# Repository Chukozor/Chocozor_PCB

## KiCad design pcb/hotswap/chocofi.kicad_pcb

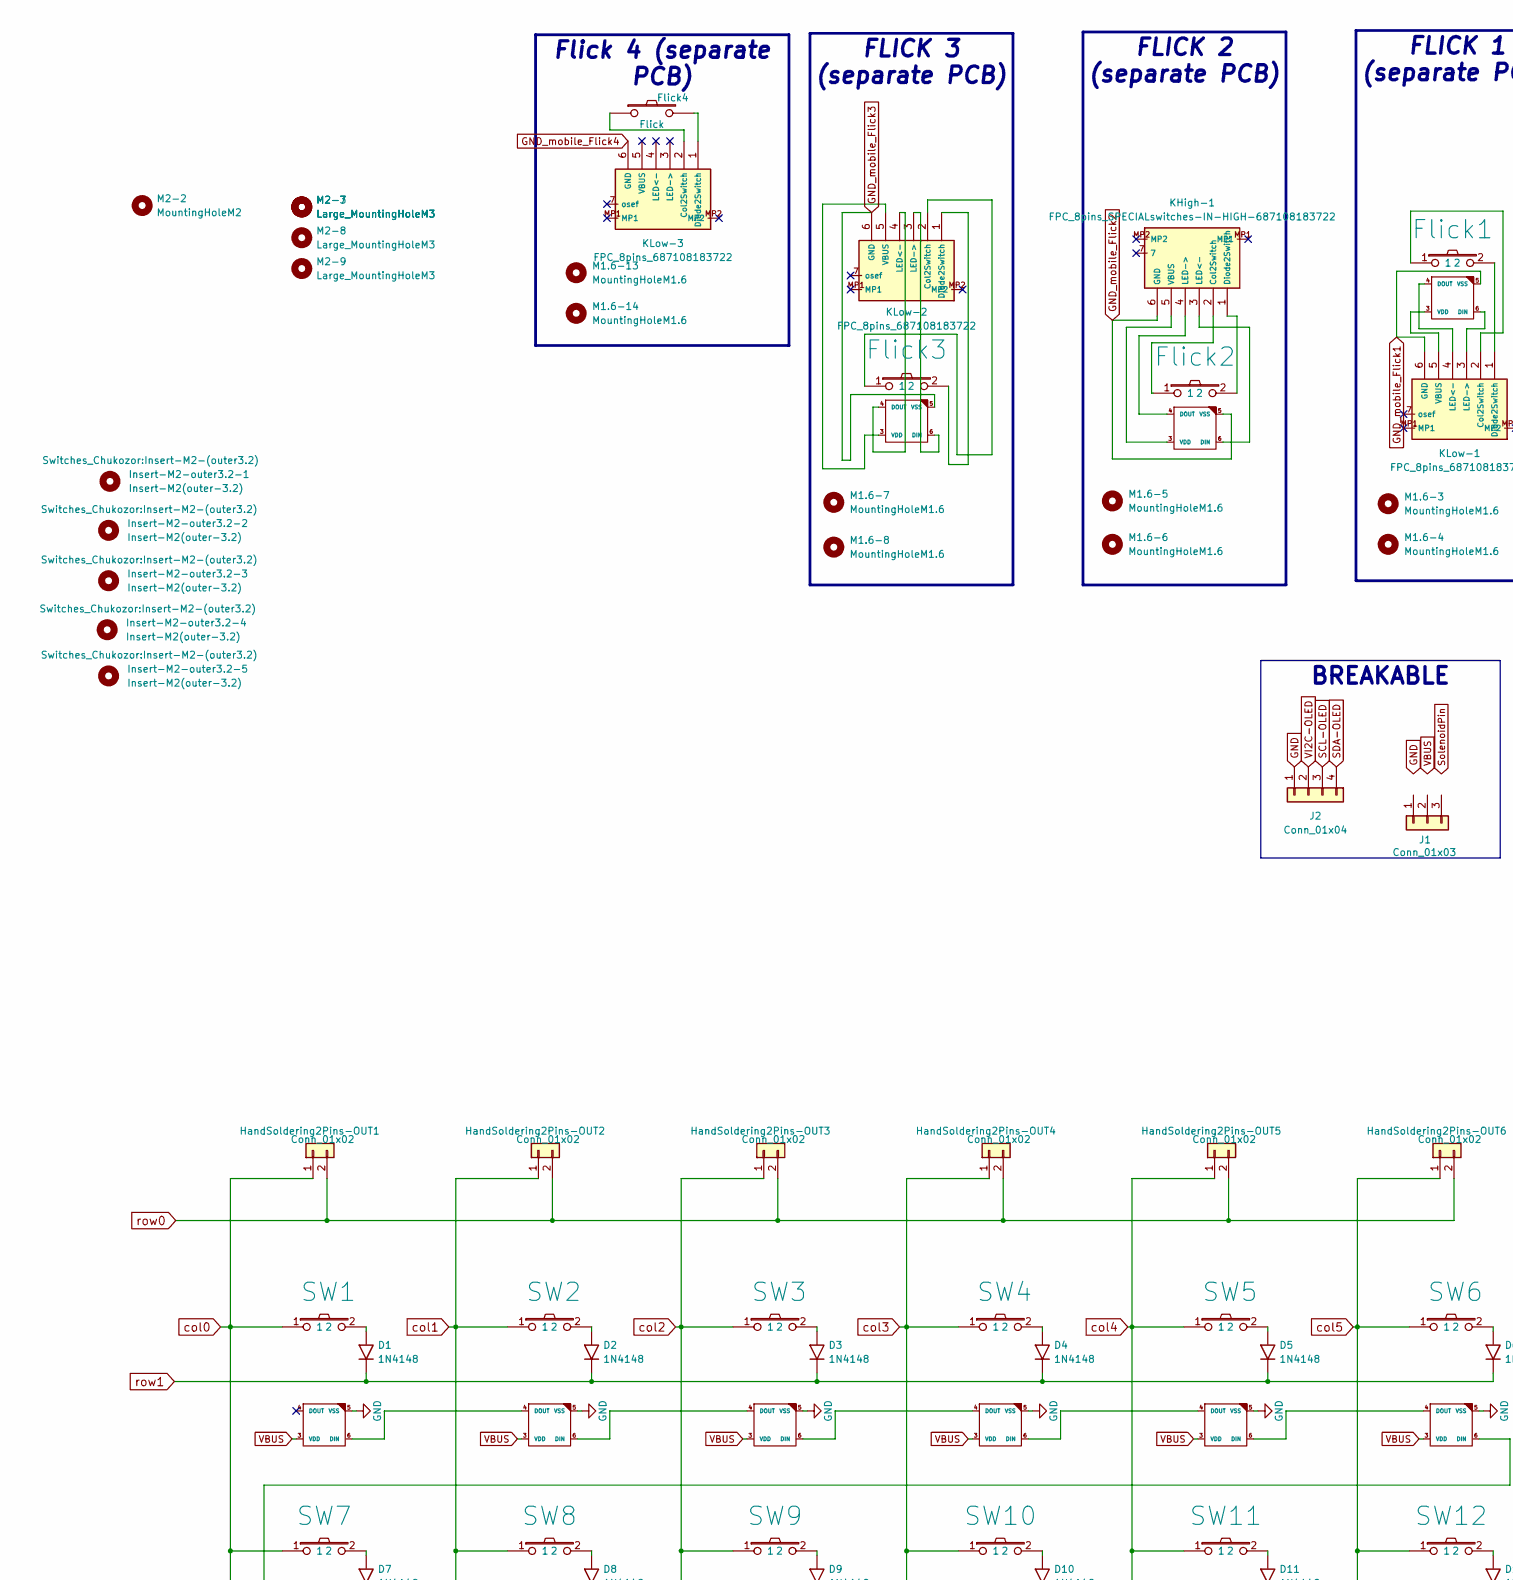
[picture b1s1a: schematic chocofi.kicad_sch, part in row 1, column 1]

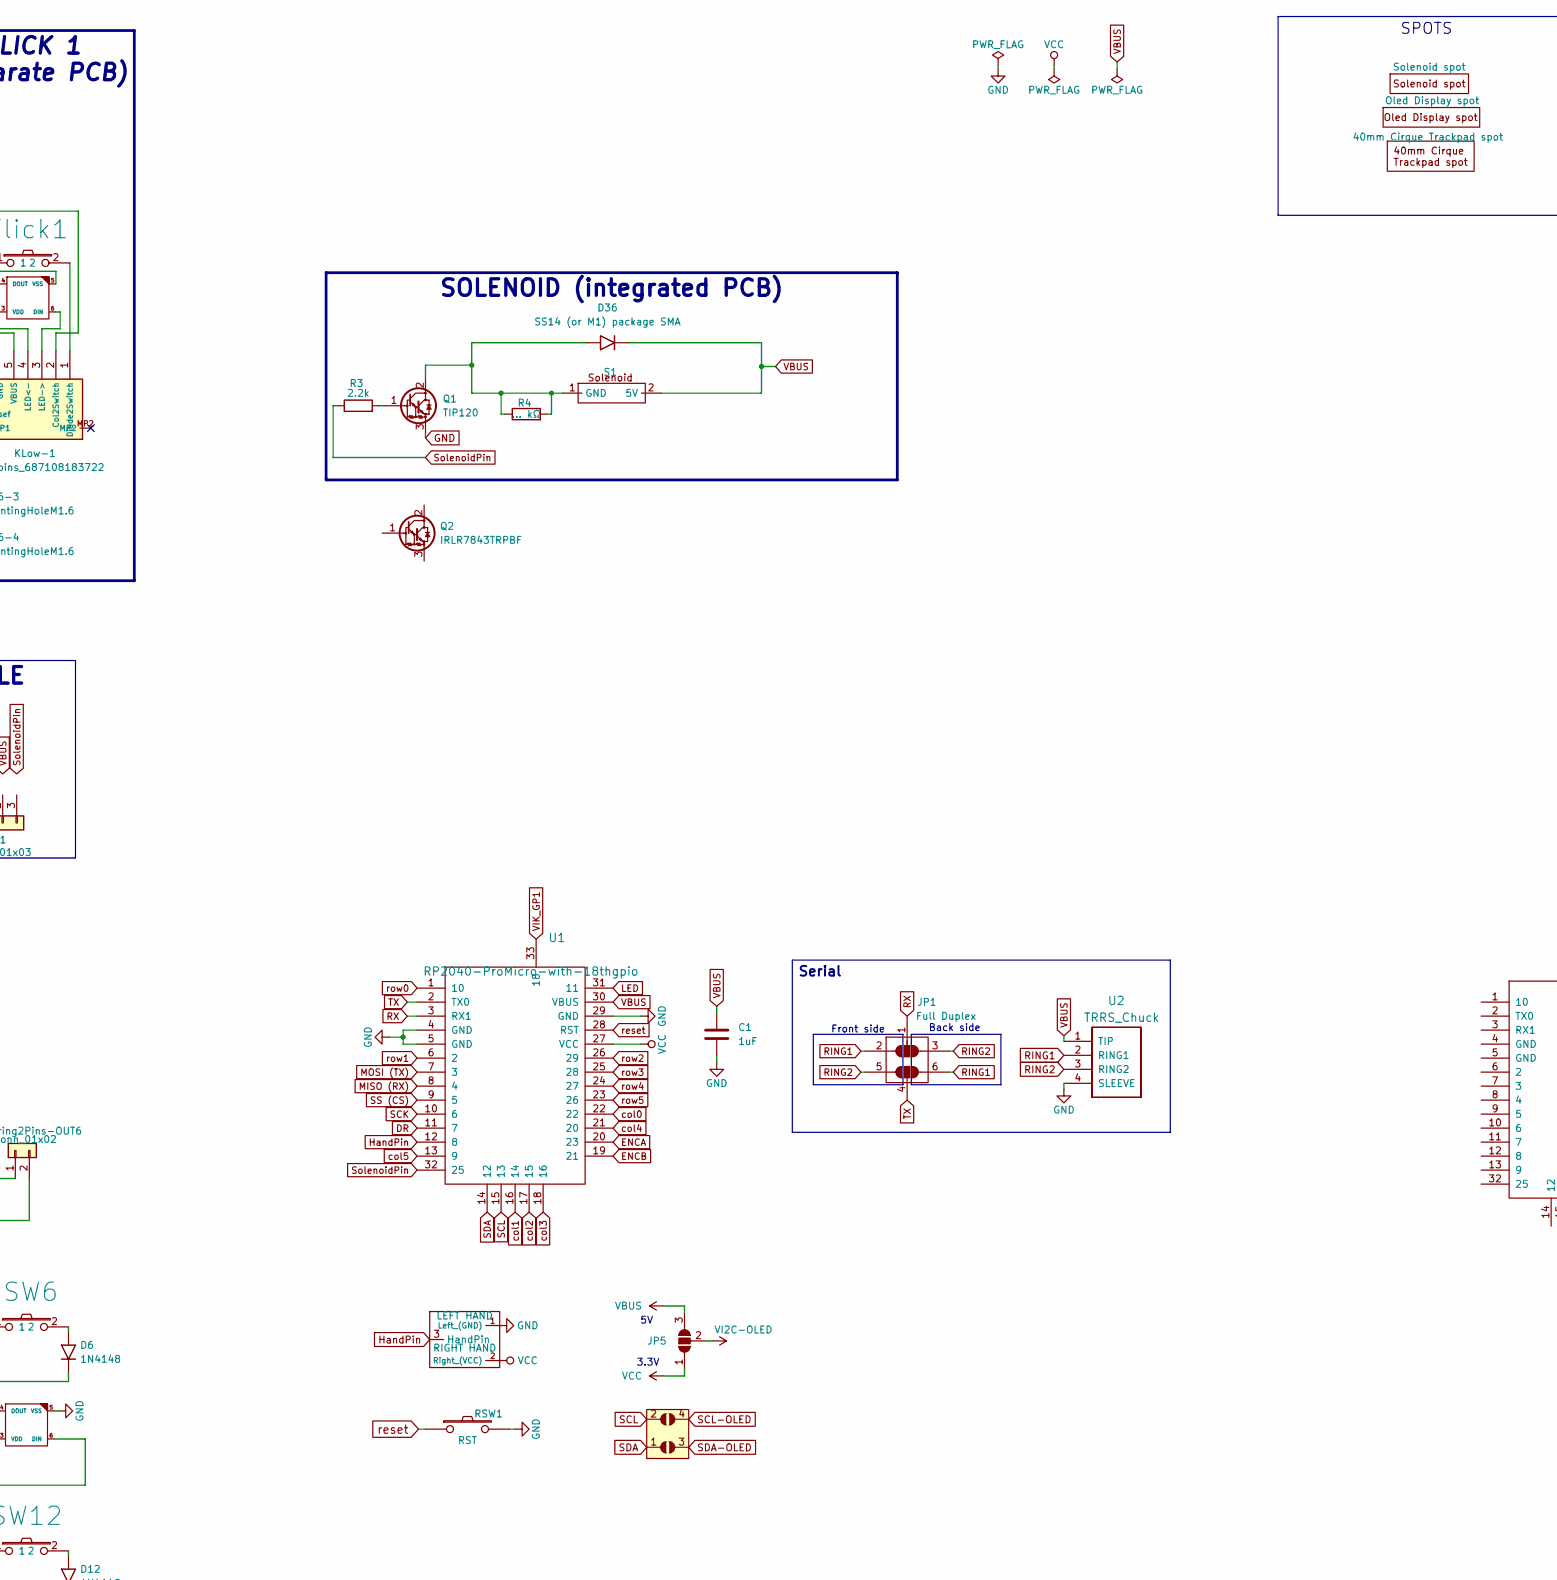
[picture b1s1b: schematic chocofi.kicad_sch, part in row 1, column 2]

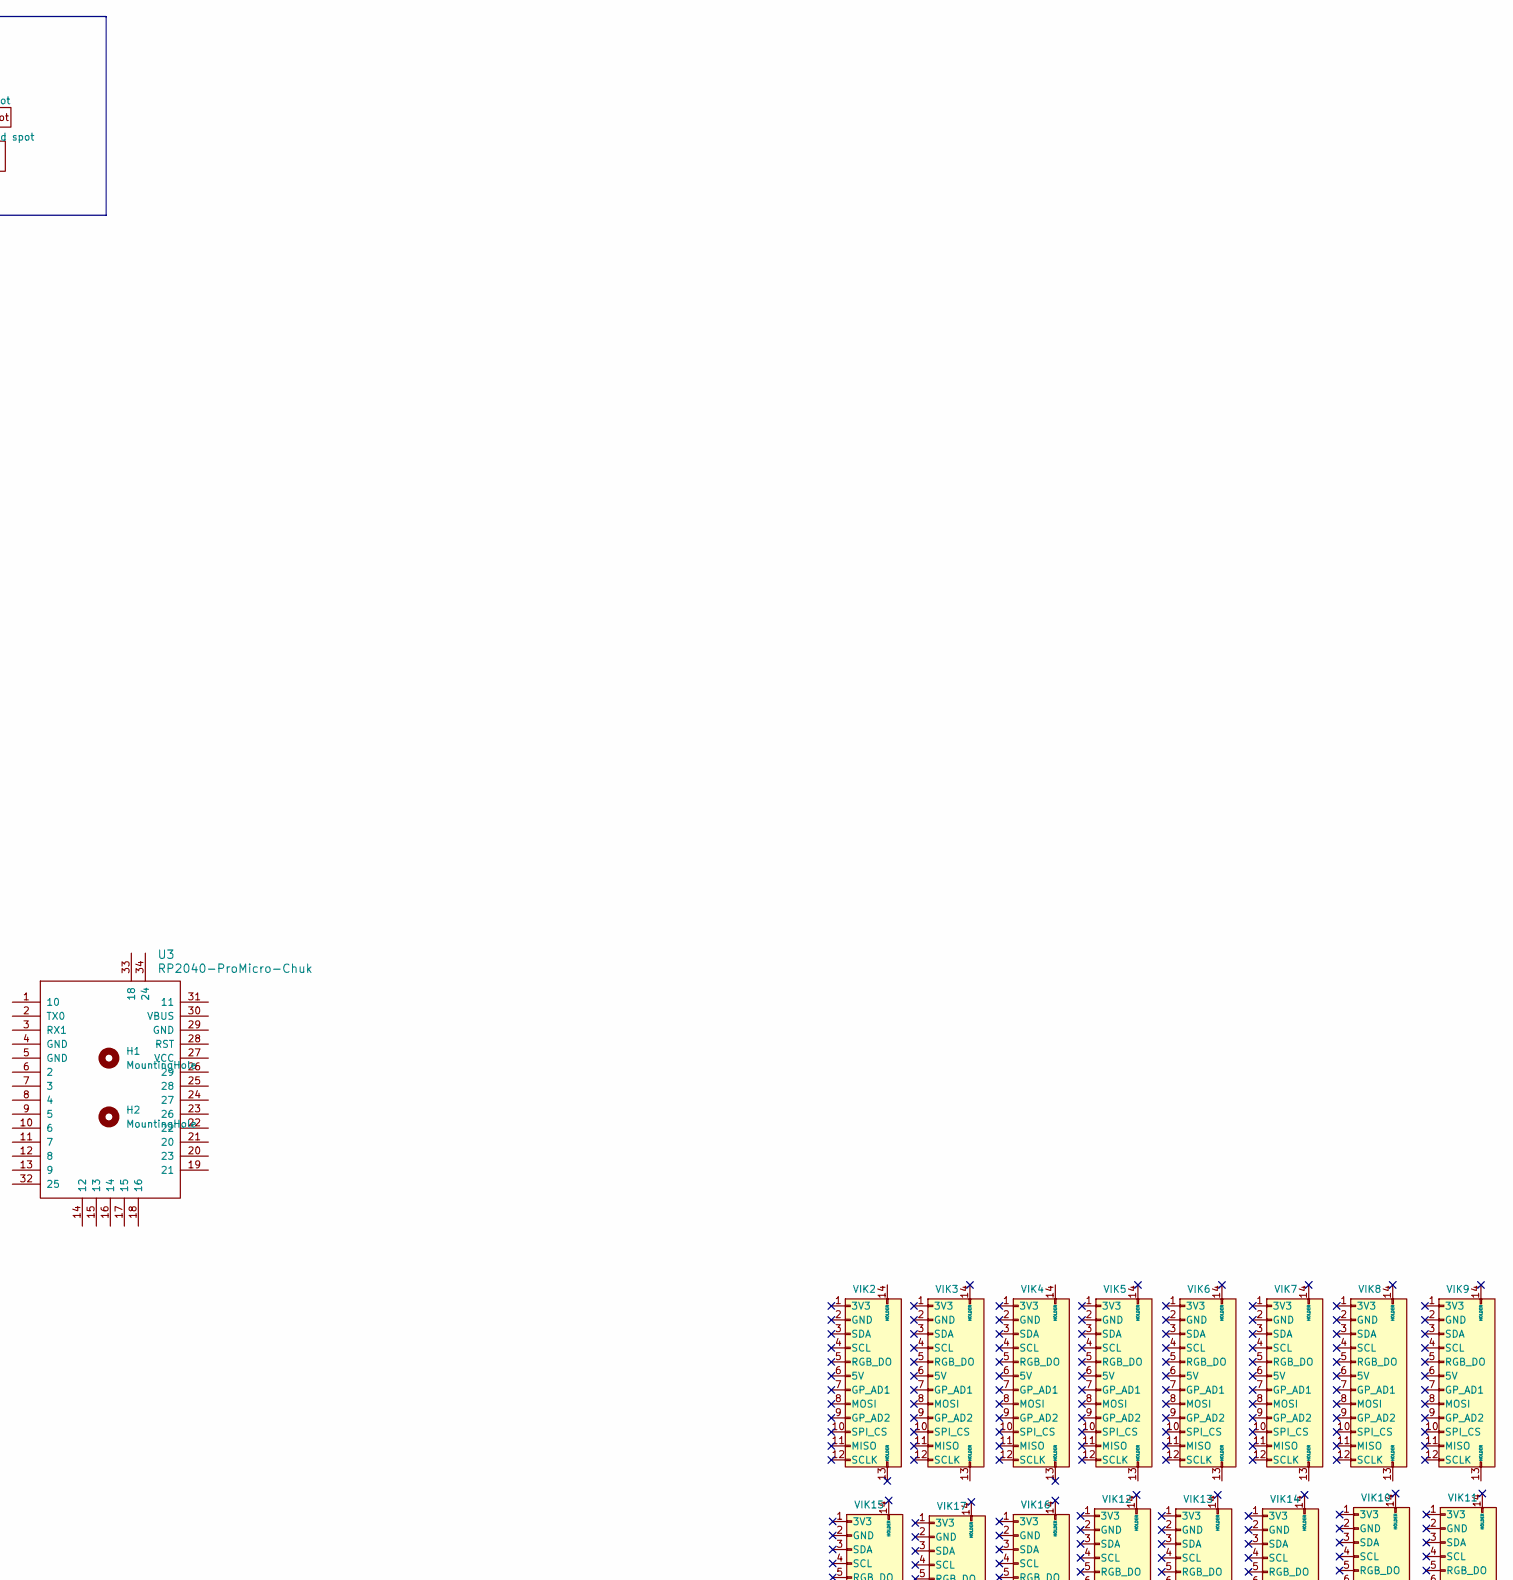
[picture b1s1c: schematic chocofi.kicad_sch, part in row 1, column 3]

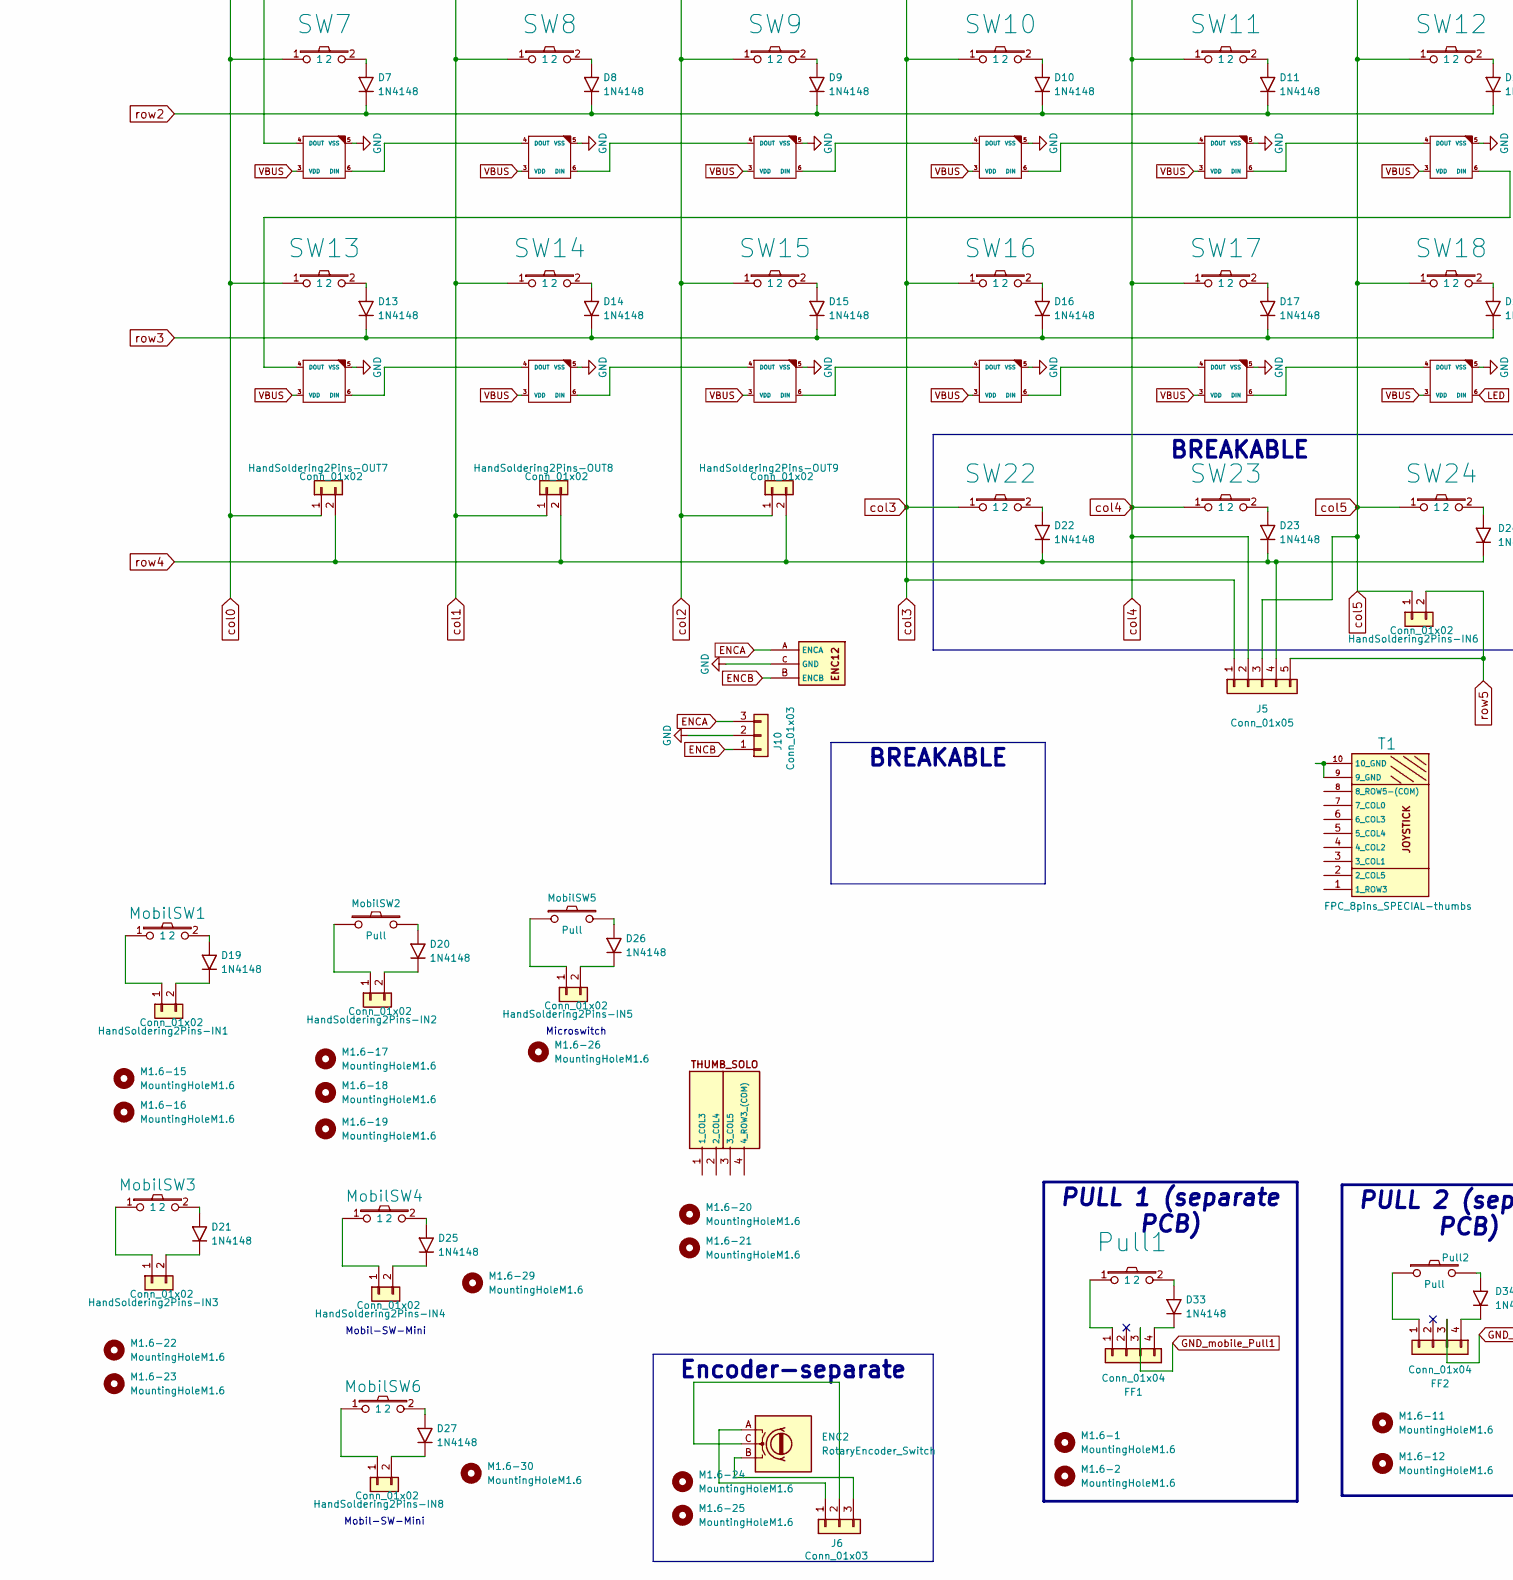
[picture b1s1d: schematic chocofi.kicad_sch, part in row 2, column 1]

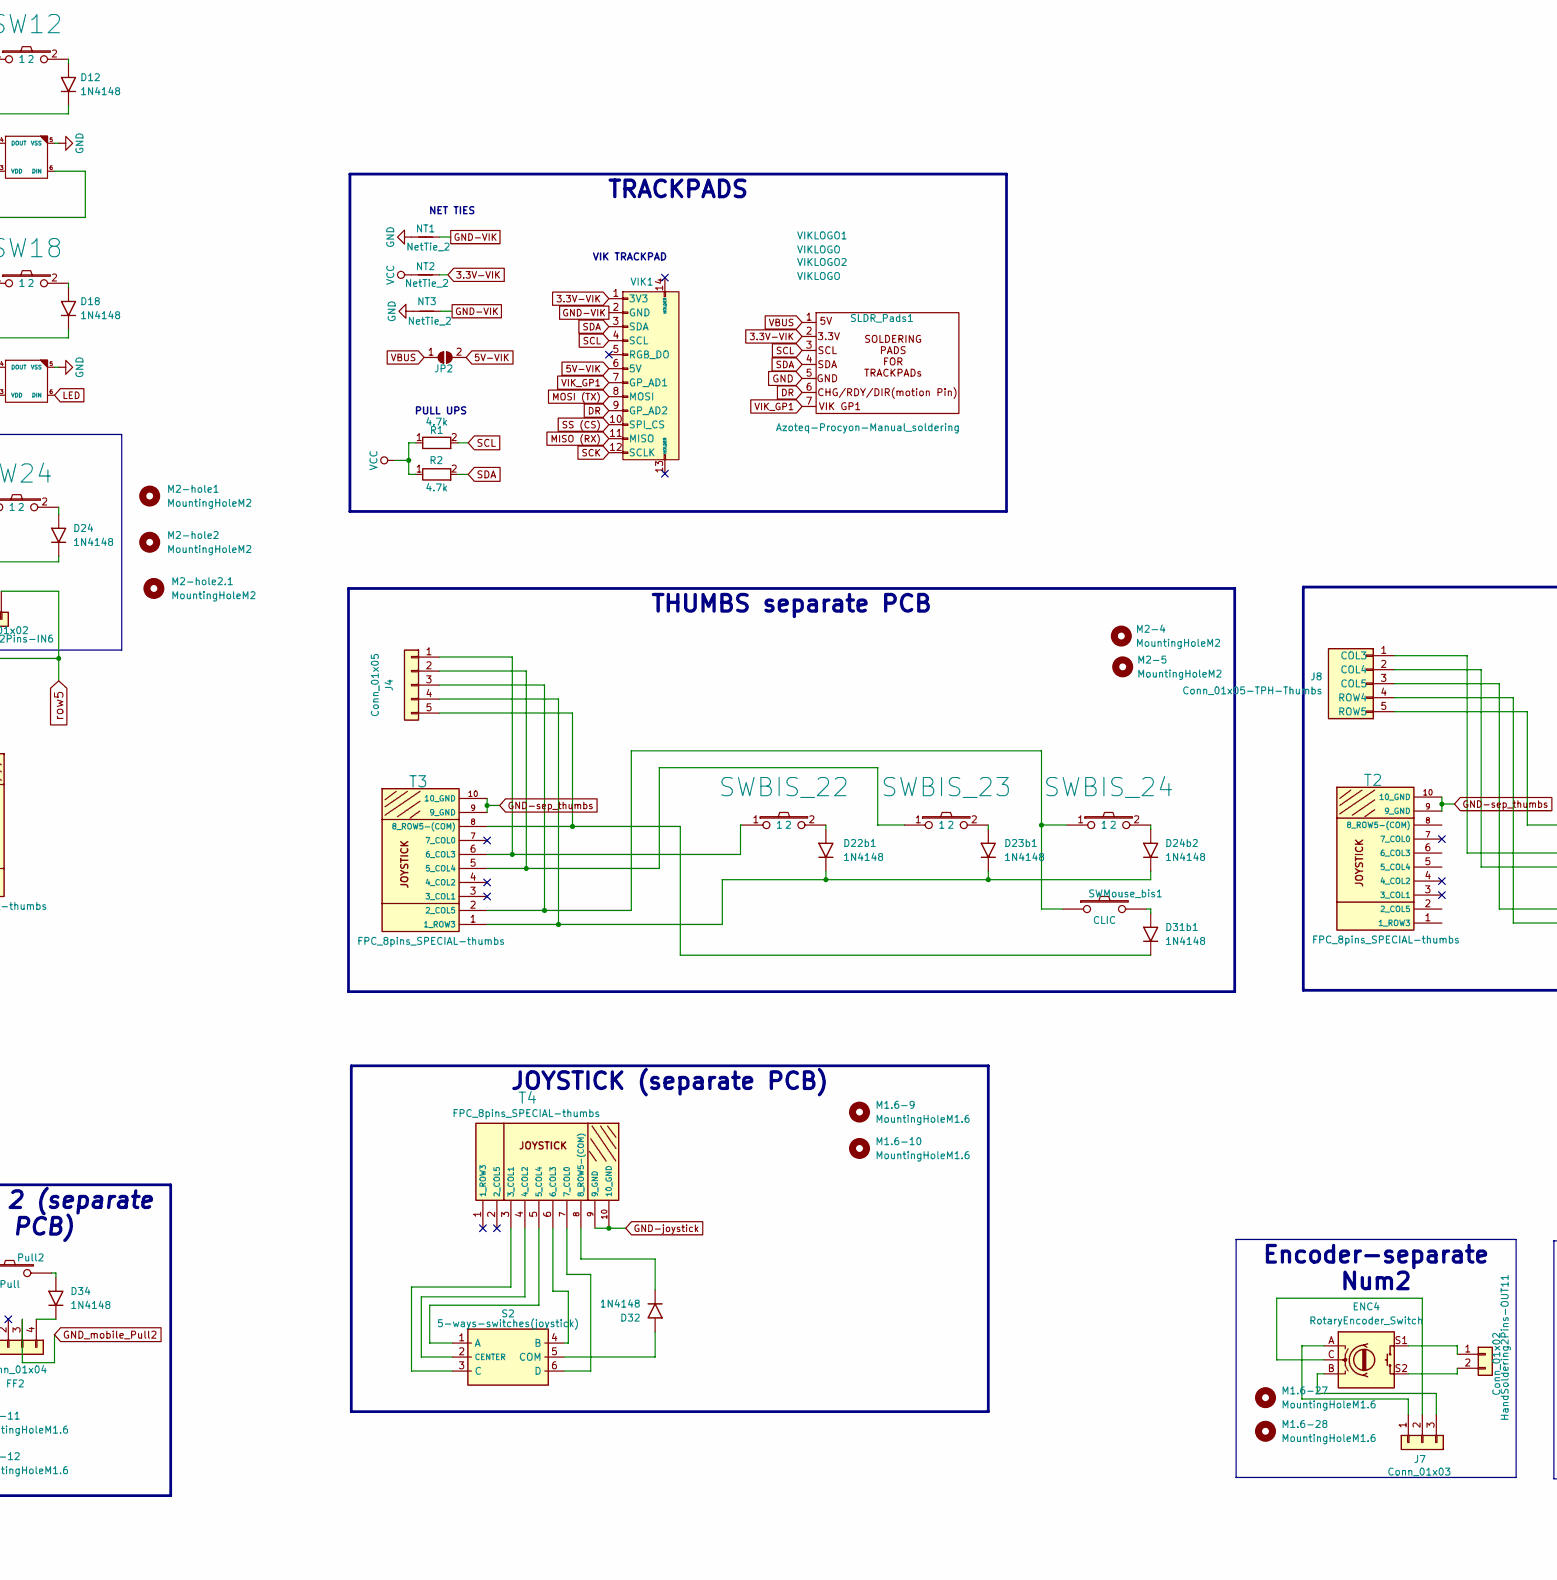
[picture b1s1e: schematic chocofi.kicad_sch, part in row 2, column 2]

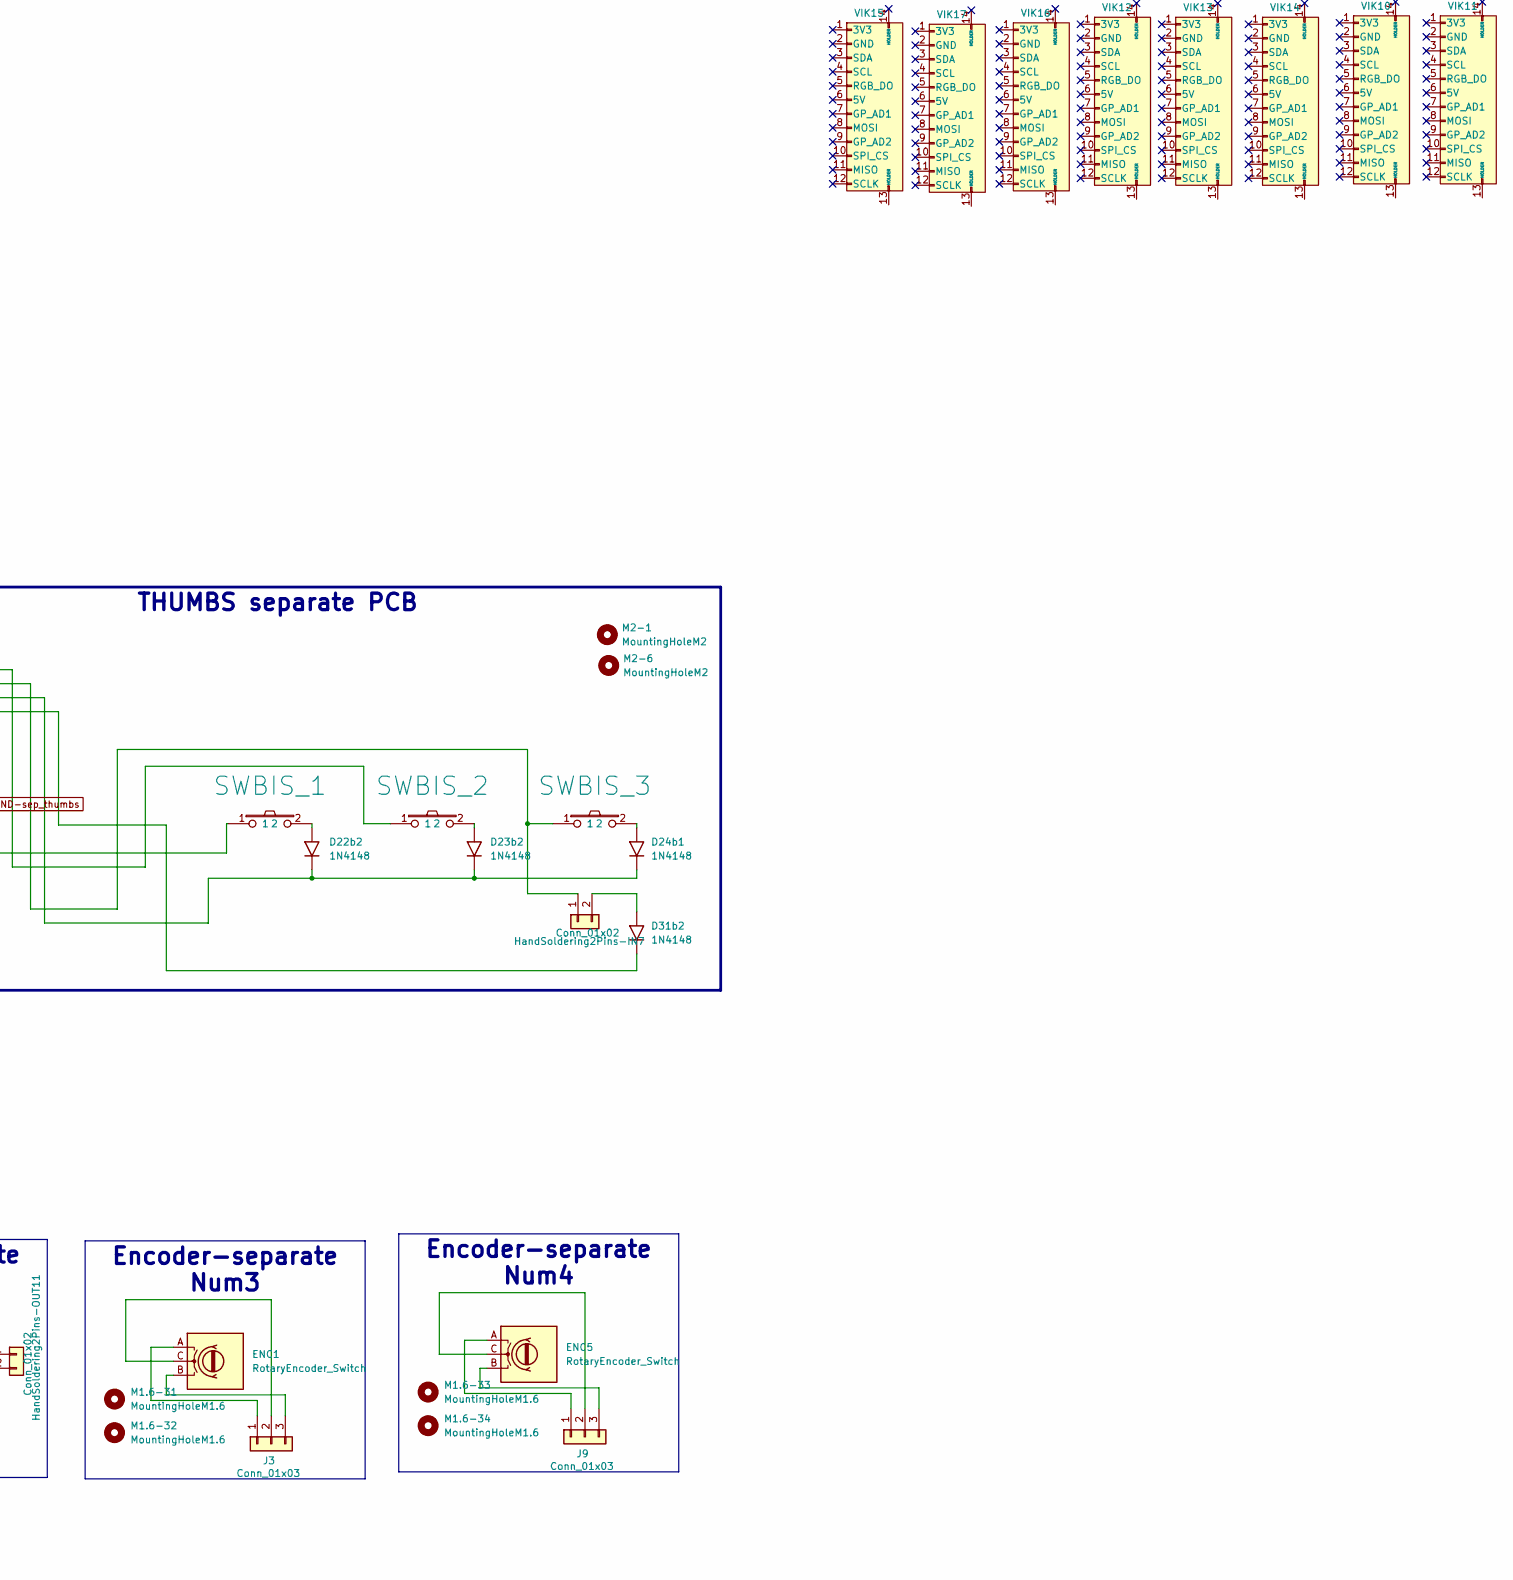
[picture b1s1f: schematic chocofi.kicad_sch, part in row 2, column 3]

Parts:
C1: 1uF; C_0805-Chuk-FA-FB
D1, D2, D3, D4, D5, D6, D7, D8, D9, D10, D11, D12, D13, D14, D15, D16, D17, D18, D22, D22b1, D22b2, D23, D23b1, D23b2, D24, D24b1, D24b2, D31b1, D31b2, D32, D34: 1N4148; SMD_SOD_123-stencil
D19, D20, D21, D25, D26, D27, D33: 1N4148; SMD_SOD_123_only_one_face
D36: SS14 (or M1) package SMA; D_SMA_Handsoldering-Chuk
ENC1, ENC4, ENC5: RotaryEncoder_Switch; RotaryEncoder_Alps_EC12E-Switch_Vertical_H20mm
ENC2: RotaryEncoder_Switch; True_EC12
ENC3: ENC12-connector; EC12-connector-SMD
FF1, FF2: Conn_01x04; FPC_4pins_Horizontal-PULL-IN_stencil
Flick1, Flick2, Flick3: SW_Chuk; Kailh_socket_PG1350_reversible_Chukozor_LED_F-MOBILE
Flick4: Flick; Microswitche-2pins
H1, H2: MountingHole; MountingHole_3.5mm
HandSoldering2Pins-IN1, HandSoldering2Pins-IN2, HandSoldering2Pins-IN3, HandSoldering2Pins-IN6, HandSoldering2Pins-IN7: Conn_01x02; HandSoldering-2pins-OUT
HandSoldering2Pins-IN4, HandSoldering2Pins-IN8: Conn_01x02; HandSoldering-2pins-OUT-SMD
HandSoldering2Pins-IN5: Conn_01x02; HandSoldering-2pins-OUT-SMD-for-microswitches
HandSoldering2Pins-OUT1, HandSoldering2Pins-OUT2, HandSoldering2Pins-OUT3, HandSoldering2Pins-OUT4, HandSoldering2Pins-OUT5, HandSoldering2Pins-OUT6: Conn_01x02; HandSoldering-2pins-reversible-OUT
HandSoldering2Pins-OUT7, HandSoldering2Pins-OUT8, HandSoldering2Pins-OUT9: Conn_01x02; HandSoldering-2pins-reversible-OUT-bottom
HandSoldering2Pins-OUT11: Conn_01x02; EC12_ribon_connector_bis2pins
Handedness1: 4.7k; R_0805_Handedness_Chukozor_assembly
Insert-M2-outer3.2-1, Insert-M2-outer3.2-2, Insert-M2-outer3.2-3, Insert-M2-outer3.2-4, Insert-M2-outer3.2-5: Insert-M2(outer-3.2); Insert-M2-(outer3.2)
J1: Conn_01x03; solenoid_ribon_connector
J2: Conn_01x04; oled_display_Chukozor_ribbon
J3, J6, J7, J9, J10: Conn_01x03; EC12_ribon_connector
J4: Conn_01x05; Thumbkeys-5pins-Mobile
J5: Conn_01x05; Thumbkeys-5pins
J8: Conn_01x05-TPH-Thumbs; Thumbkeys-5pins-Mobile
JP1: Full Duplex; SolderJumper-2_Open_Chuck
JP2: 5V-VIK; SB-small
JP5: VI2C-OLED; SB-3pins-small
K2: FPC_8p_SPECIAL-thumbs-or-joystick; Kailh_socket_PG1350_reversible_Chukozor_THUMBS-SOLO
KHigh-1: FPC_8pins_SPECIALswitches-IN-HIGH-687108183722; FPC_8pins_687108183722_reversible-Mobile-IN-TOPP-FROMABOVE-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; Mouser Part Number 710-687108183722
KLow-1, KLow-3: FPC_8pins_687108183722; FPC_8pins_687108183722_reversible-Mobile-IN-LOW-FROMBELOW_S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; Mouser Part Number 710-687108183722
KLow-2: FPC_8pins_687108183722; FPC_8pins_687108183722_reversible-Mobile-IN-TOPP-FROMBELOW; Mouser Part Number 710-687108183722
M1.6-1, M1.6-2, M1.6-3, M1.6-4, M1.6-5, M1.6-6, M1.6-7, M1.6-8, M1.6-9, M1.6-10, M1.6-11, M1.6-12, M1.6-13, M1.6-14, M1.6-15, M1.6-16, M1.6-17, M1.6-18, M1.6-19, M1.6-20, M1.6-21, M1.6-22, M1.6-23, M1.6-24, M1.6-25, M1.6-26, M1.6-27, M1.6-28, M1.6-29, M1.6-30: MountingHoleM1.6; Mounting-hole-M1.6
M1.6-31, M1.6-32, M1.6-33, M1.6-34: MountingHoleM1.6; Mounting-hole-M1.6-withLarge2mm_Hole
M2-1, M2-2, M2-4, M2-5, M2-6, M2-hole1, M2-hole2, M2-hole2.1: MountingHoleM2; Mounting-hole-M2
M2-3, M2-7, M2-8, M2-9: Large_MountingHoleM3; Mounting-hole-M2-hole3
MobilSW1, MobilSW3: Pull; Kailh_socket_PG1350_reversible_Chukozor_-PULL-simplifiev2
MobilSW2: Pull; Microswitche-2pins-V2
MobilSW4, MobilSW6: Pull; Kailh_socket_PG1350_reversible_Chukozor_-PULL-simplifiev2-T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
MobilSW5: Pull; Microswitche-2pins-V3
NT1: NetTie_2; NetTie-2_SMD_Pad0.5mm
NT2, NT3: NetTie_2; NetTie-2_SMD_Pad0.5mm-long
Pull1: Pull; Kailh_socket_PG1350_reversible_Chukozor_-PULL-simplifiev2
Pull2: Pull; Microswitche-2pins
Q1: TIP120; D-PAK(TO252)(improved-and-reversible)
Q2: IRLR7843TRPBF; D-PAK(TO252)
R1, R2: 4.7k; R_0805_double_face_Chukozor_assembly
R3: 2.2k; R_0805_double_face_Chukozor-HotPlateSoldering
R4: ... kΩ; R_0805_double_face_Chukozor-Optional
RSW1: RST; SW_SMD_4x4mm-reversible(unconnected)
S1: Solenoid-PinHeader_1x02_P2.54mm_Vertical-Chuk
S2: 5-ways-switches(joystick); QUE-JOYSTICK-UNE-FACE(non reversible-pourvA); Mouser Part Number 688-SKRHAC
SB3: Oled; SB-x2-small
SLDR_Pads1: Azoteq-Procyon-Manual_soldering
SW1, SW7, SW13: SW_Chuk; Kailh_socket_PG1350_reversible_Chukozor_LED_F_6thcolumn
SW2, SW3, SW4, SW5, SW8, SW9, SW10, SW11, SW14, SW15, SW16, SW17: SW_Chuk; Kailh_socket_PG1350_reversible_Chukozor_LED_F
SW6, SW12, SW18: SW_Chuk; Kailh_socket_PG1350_reversible_Chukozor_LED_F_contreMCU
SW22, SW24: Pull; Kailh_socket_PG1350_reversible_Chukozor_THUMBS_ext
SW23: Pull; Kailh_socket_PG1350_reversible_Chukozor_THUMBS
SWBIS_1, SWBIS_2, SWBIS_3, SWBIS_22, SWBIS_23, SWBIS_24: Pull; Kailh_socket_PG1350_reversible_Chukozor_THUMBS_ext
SWMouse_bis1: CLIC; Microswitche-2pins
Spot1: 40mm Cirque Trackpad spot; Spot-Cirque_Trackpad_40mm
Spot2: Solenoid spot; Spot-Solenoid
Spot3: Oled Display spot; Spot-Oled-display-I2C
T1: FPC_8pins_SPECIAL-thumbs; FPC_10p-reversible-ThumbORJoystick-OUT
T2, T3: FPC_8pins_SPECIAL-thumbs; FPC_10p-reversible-ThumbORJoystick-IN
T4: FPC_8pins_SPECIAL-thumbs; FPC_10p-reversible-QUE-JOYSTICK-IN(non reversible-vA)
U1: RP2040-ProMicro-with-18thgpio; RP2040-ProMicro-Chuk-with-18thgpio-silkadjust
U2: TRRS_Chuck; MJ-4PP-9_Chukozor-3
U3: RP2040-ProMicro-Chuk; RP2040-ProMicro-breadboard
VIK1, VIK2, VIK3, VIK4, VIK5, VIK6, VIK7, VIK8, VIK9, VIK10, VIK11, VIK12, VIK13, VIK14, VIK15, VIK16, VIK17: vik-keyboard-connector-horizontal-Both-Sides
VIKLOGO1, VIKLOGO2: VIKLOGO; vik-logo-small

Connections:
3.3V-VIK: NT2.2, SLDR_Pads1.2 (3.3V), VIK1.1 (3V3)
5V-VIK: JP2.2 (B), VIK1.6 (5V)
DR: SLDR_Pads1.6 (CHG/DIR/RDY), U1.11 (7), VIK1.9 (GP_AD2)
ENCA: ENC3.A (ENCA), J10.3, U1.20 (23)
ENCB: ENC3.B (ENCB), J10.1, U1.19 (21)
GND: C1.2, ENC3.C (GND), Handedness1.1 (Left_(GND)), J2.1 (Pin_4), J10.2, NT1.1, NT3.1, Q1.3 (E), RSW1.2, SLDR_Pads1.5 (GND), SW1.5 (VSS), SW2.5 (VSS), SW3.5 (VSS), SW4.5 (VSS), SW5.5 (VSS), SW6.5 (VSS), SW7.5 (VSS), SW8.5 (VSS), SW9.5 (VSS), SW10.5 (VSS), SW11.5 (VSS), SW12.5 (VSS), SW13.5 (VSS), SW14.5 (VSS), SW15.5 (VSS), SW16.5 (VSS), SW17.5 (VSS), SW18.5 (VSS), U1.4 (GND), U1.5 (GND), U1.29 (GND), U2.4 (SLEEVE)
GND-VIK: NT1.2, NT3.2, VIK1.2 (GND)
GND-joystick: T4.9 (9_GND), T4.10 (10_GND)
GND-sep_thumbs: T2.9 (9_GND), T2.10 (10_GND), T3.9 (9_GND), T3.10 (10_GND)
GND_mobile_Flick1: Flick1.5 (VSS), KLow-1.6 (GND)
GND_mobile_Flick2: Flick2.5 (VSS), KHigh-1.6 (GND)
GND_mobile_Flick3: Flick3.5 (VSS), KLow-2.6 (GND)
GND_mobile_Flick4: KLow-3.6 (GND)
GND_mobile_Pull1: FF1.3 (Pin_2)
GND_mobile_Pull2: FF2.3 (Pin_2)
HandPin: Handedness1.3 (HandPin), U1.12 (8)
LED: SW18.6 (DIN), U1.31 (11)
MISO (RX): U1.8 (4), VIK1.11 (MISO)
MOSI (TX): U1.7 (3), VIK1.8 (MOSI)
unnamed: D1.2 (A), SW1.2
unnamed: D2.2 (A), SW2.2
unnamed: D3.2 (A), SW3.2
unnamed: D4.2 (A), SW4.2
unnamed: D5.2 (A), SW5.2
unnamed: D6.2 (A), SW6.2
unnamed: D7.2 (A), SW7.2
unnamed: D8.2 (A), SW8.2
unnamed: D9.2 (A), SW9.2
unnamed: D10.2 (A), SW10.2
unnamed: D11.2 (A), SW11.2
unnamed: D12.2 (A), SW12.2
unnamed: D13.2 (A), SW13.2
unnamed: D14.2 (A), SW14.2
unnamed: D15.2 (A), SW15.2
unnamed: D16.2 (A), SW16.2
unnamed: D17.2 (A), SW17.2
unnamed: D18.2 (A), SW18.2
unnamed: D19.2 (A), MobilSW1.2
unnamed: D19.1 (K), HandSoldering2Pins-IN1.2
unnamed: D20.2 (A), MobilSW2.2
unnamed: D20.1 (K), HandSoldering2Pins-IN2.2
unnamed: D21.2 (A), MobilSW3.2
unnamed: D21.1 (K), HandSoldering2Pins-IN3.2
unnamed: D22.2 (A), SW22.2
unnamed: D22b1.2 (A), SWBIS_22.2
unnamed: D22b1.1 (K), D23b1.1 (K), D24b2.1 (K), J4.4, T3.1 (1_ROW3)
unnamed: D22b2.2 (A), SWBIS_1.2
unnamed: D22b2.1 (K), D23b2.1 (K), D24b1.1 (K), J8.4 (ROW4)
unnamed: D23.2 (A), SW23.2
unnamed: D23b1.2 (A), SWBIS_23.2
unnamed: D23b2.2 (A), SWBIS_2.2
unnamed: D24.2 (A), SW24.2
unnamed: D24b1.2 (A), SWBIS_3.2
unnamed: D24b2.2 (A), SWBIS_24.2
unnamed: D25.2 (A), MobilSW4.2
unnamed: D25.1 (K), HandSoldering2Pins-IN4.2
unnamed: D26.2 (A), MobilSW5.2
unnamed: D26.1 (K), HandSoldering2Pins-IN5.2
unnamed: D27.2 (A), MobilSW6.2
unnamed: D27.1 (K), HandSoldering2Pins-IN8.2
unnamed: D31b1.2 (A), SWMouse_bis1.2
unnamed: D31b1.1 (K), J4.5, T3.8 (8_ROW5-(COM))
unnamed: D31b2.2 (A), HandSoldering2Pins-IN7.2
unnamed: D31b2.1 (K), J8.5 (ROW5)
unnamed: D32.2 (A), S2.5 (COM)
unnamed: D32.1 (K), T4.8 (8_ROW5-(COM))
unnamed: D33.2 (A), Pull1.2
unnamed: D33.1 (K), FF1.4 (Pin_1)
unnamed: D34.2 (A), Pull2.2
unnamed: D34.1 (K), FF2.4 (Pin_1)
unnamed: D36.2 (A), Q1.2 (C), R4.1, R4.2, S1.1 (GND)
unnamed: FF1.1 (Pin_4), Pull1.1
unnamed: FF2.1 (Pin_4), Pull2.1
unnamed: Flick1.6 (DIN), KLow-1.3 (LED->)
unnamed: Flick1.4 (DOUT), KLow-1.4 (LED<-)
unnamed: Flick1.3 (VDD), KLow-1.5 (VBUS)
unnamed: Flick2.6 (DIN), KHigh-1.3 (LED<-)
unnamed: Flick2.4 (DOUT), KHigh-1.4 (LED->)
unnamed: Flick2.3 (VDD), KHigh-1.5 (VBUS)
unnamed: Flick3.6 (DIN), KLow-2.3 (LED->)
unnamed: Flick3.4 (DOUT), KLow-2.4 (LED<-)
unnamed: Flick3.3 (VDD), KLow-2.5 (VBUS)
unnamed: HandSoldering2Pins-IN1.1, MobilSW1.1
unnamed: HandSoldering2Pins-IN2.1, MobilSW2.1
unnamed: HandSoldering2Pins-IN3.1, MobilSW3.1
unnamed: HandSoldering2Pins-IN4.1, MobilSW4.1
unnamed: HandSoldering2Pins-IN5.1, MobilSW5.1
unnamed: HandSoldering2Pins-IN7.1, J8.3 (COL5), SWBIS_3.1
unnamed: HandSoldering2Pins-IN8.1, MobilSW6.1
unnamed: ENC4.S1, HandSoldering2Pins-OUT11.1
unnamed: ENC4.S2, HandSoldering2Pins-OUT11.2
unnamed: ENC1.A, J3.1
unnamed: ENC1.C, J3.2
unnamed: ENC1.B, J3.3
unnamed: J4.1, SWBIS_22.1, T3.6 (6_COL3)
unnamed: J4.2, SWBIS_23.1, T3.5 (5_COL4)
unnamed: J4.3, SWBIS_24.1, SWMouse_bis1.1, T3.2 (2_COL5)
unnamed: ENC2.A, J6.1
unnamed: ENC2.C, J6.2
unnamed: ENC2.B, J6.3
unnamed: ENC4.A, J7.1
unnamed: ENC4.C, J7.2
unnamed: ENC4.B, J7.3
unnamed: J8.1 (COL3), SWBIS_1.1
unnamed: J8.2 (COL4), SWBIS_2.1
unnamed: ENC5.A, J9.1
unnamed: ENC5.C, J9.2
unnamed: ENC5.B, J9.3
unnamed: Flick2.1, KHigh-1.2 (Col2Switch)
unnamed: Flick2.2, KHigh-1.1 (Diode2Switch)
unnamed: Flick1.1, KLow-1.2 (Col2Switch)
unnamed: Flick1.2, KLow-1.1 (Diode2Switch)
unnamed: Flick3.1, KLow-2.2 (Col2Switch)
unnamed: Flick3.2, KLow-2.1 (Diode2Switch)
unnamed: Flick4.1, KLow-3.2 (Col2Switch)
unnamed: Flick4.2, KLow-3.1 (Diode2Switch)
unnamed: Q1.1 (B), R3.2
unnamed: S2.1 (A), T4.5 (5_COL4)
unnamed: S2.4 (B), T4.6 (6_COL3)
unnamed: S2.3 (C), T4.3 (3_COL1)
unnamed: S2.2 (CENTER), T4.4 (4_COL2)
unnamed: S2.6 (D), T4.7 (7_COL0)
unnamed: SW1.6 (DIN), SW2.4 (DOUT)
unnamed: SW2.6 (DIN), SW3.4 (DOUT)
unnamed: SW3.6 (DIN), SW4.4 (DOUT)
unnamed: SW4.6 (DIN), SW5.4 (DOUT)
unnamed: SW5.6 (DIN), SW6.4 (DOUT)
unnamed: SW6.6 (DIN), SW7.4 (DOUT)
unnamed: SW7.6 (DIN), SW8.4 (DOUT)
unnamed: SW8.6 (DIN), SW9.4 (DOUT)
unnamed: SW10.6 (DIN), SW11.4 (DOUT)
unnamed: SW9.6 (DIN), SW10.4 (DOUT)
unnamed: SW11.6 (DIN), SW12.4 (DOUT)
unnamed: SW12.6 (DIN), SW13.4 (DOUT)
unnamed: SW13.6 (DIN), SW14.4 (DOUT)
unnamed: SW14.6 (DIN), SW15.4 (DOUT)
unnamed: SW15.6 (DIN), SW16.4 (DOUT)
unnamed: SW16.6 (DIN), SW17.4 (DOUT)
unnamed: SW17.6 (DIN), SW18.4 (DOUT)
unnamed: T1.9 (9_GND), T1.10 (10_GND)
RING1: JP1.2 (A), JP1.6 (B), U2.2 (RING1)
RING2: JP1.3 (B), JP1.5 (A), U2.3 (RING2)
RX: JP1.1 (C), U1.3 (RX1)
SCK: U1.10 (6), VIK1.12 (SCLK)
SCL: R1.2, SB3.2 (B), SLDR_Pads1.3 (SCL), U1.15 (13), VIK1.4 (SCL)
SCL-OLED: J2.3 (Pin_2), SB3.4 (A)
SDA: R2.2, SB3.1 (B), SLDR_Pads1.4 (SDA), U1.14 (12), VIK1.3 (SDA)
SDA-OLED: J2.4 (Pin_1), SB3.3 (A)
SS (CS): U1.9 (5), VIK1.10 (SPI_CS)
SolenoidPin: R3.1, U1.32 (25)
TX: JP1.4 (C), U1.2 (TX0)
VBUS: C1.1, D36.1 (K), JP2.1 (A), JP5.3 (B), S1.2 (5V), SLDR_Pads1.1 (3.3V), SW1.3 (VDD), SW2.3 (VDD), SW3.3 (VDD), SW4.3 (VDD), SW5.3 (VDD), SW6.3 (VDD), SW7.3 (VDD), SW8.3 (VDD), SW9.3 (VDD), SW10.3 (VDD), SW11.3 (VDD), SW12.3 (VDD), SW13.3 (VDD), SW14.3 (VDD), SW15.3 (VDD), SW16.3 (VDD), SW17.3 (VDD), SW18.3 (VDD), U1.30 (VBUS), U2.1 (TIP)
VCC: Handedness1.2 (Right_(VCC)), JP5.1 (A), NT2.1, R1.1, R2.1, U1.27 (VCC)
VI2C-OLED: J2.2 (Pin_3), JP5.2 (C)
VIK_GP1: SLDR_Pads1.7 (CHG/DIR/RDY), U1.33 (18), VIK1.7 (GP_AD1)
col0: HandSoldering2Pins-OUT1.1, HandSoldering2Pins-OUT7.1, SW1.1, SW7.1, SW13.1, U1.22
col1: HandSoldering2Pins-OUT2.1, HandSoldering2Pins-OUT8.1, SW2.1, SW8.1, SW14.1, U1.16 (14)
col2: HandSoldering2Pins-OUT3.1, HandSoldering2Pins-OUT9.1, SW3.1, SW9.1, SW15.1, U1.17 (15)
col3: HandSoldering2Pins-OUT4.1, J5.1, SW4.1, SW10.1, SW16.1, SW22.1, U1.18 (16)
col4: HandSoldering2Pins-OUT5.1, J5.2, SW5.1, SW11.1, SW17.1, SW23.1, U1.21 (20)
col5: HandSoldering2Pins-IN6.1, HandSoldering2Pins-OUT6.1, J5.3, SW6.1, SW12.1, SW18.1, SW24.1, U1.13 (9)
reset: RSW1.1, U1.28 (RST)
row0: HandSoldering2Pins-OUT1.2, HandSoldering2Pins-OUT2.2, HandSoldering2Pins-OUT3.2, HandSoldering2Pins-OUT4.2, HandSoldering2Pins-OUT5.2, HandSoldering2Pins-OUT6.2, U1.1 (10)
row1: D1.1 (K), D2.1 (K), D3.1 (K), D4.1 (K), D5.1 (K), D6.1 (K), U1.6 (2)
row2: D7.1 (K), D8.1 (K), D9.1 (K), D10.1 (K), D11.1 (K), D12.1 (K), U1.26 (29)
row3: D13.1 (K), D14.1 (K), D15.1 (K), D16.1 (K), D17.1 (K), D18.1 (K), U1.25 (28)
row4: D22.1 (K), D23.1 (K), D24.1 (K), HandSoldering2Pins-OUT7.2, HandSoldering2Pins-OUT8.2, HandSoldering2Pins-OUT9.2, J5.4, U1.24 (27)
row5: HandSoldering2Pins-IN6.2, J5.5, U1.23 (26)

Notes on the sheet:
Back side
Mobil-SW-Mini
VIK TRACKPAD
NET TIES
PULL UPS
Front side
Microswitch
3.3V
PULL 2 (separate PCB)
Encoder-separate Num3
FLICK 1 (separate PCB)
BREAKABLE
Flick 4 (separate PCB)
FLICK 3 (separate PCB)
SPOTS
PULL 1 (separate PCB)
TRACKPADS
SOLENOID (integrated PCB)
THUMBS separate PCB
Encoder-separate Num2
FLICK 2 (separate PCB)
Encoder-separate
Serial
JOYSTICK (separate PCB)
Encoder-separate Num4

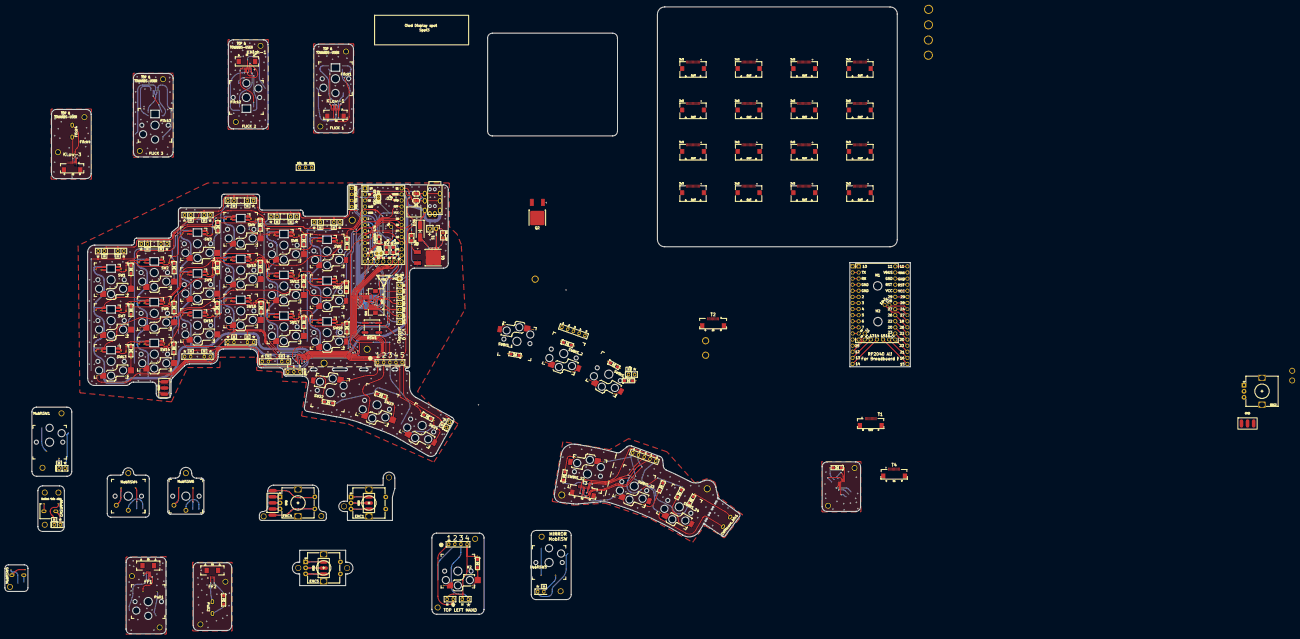
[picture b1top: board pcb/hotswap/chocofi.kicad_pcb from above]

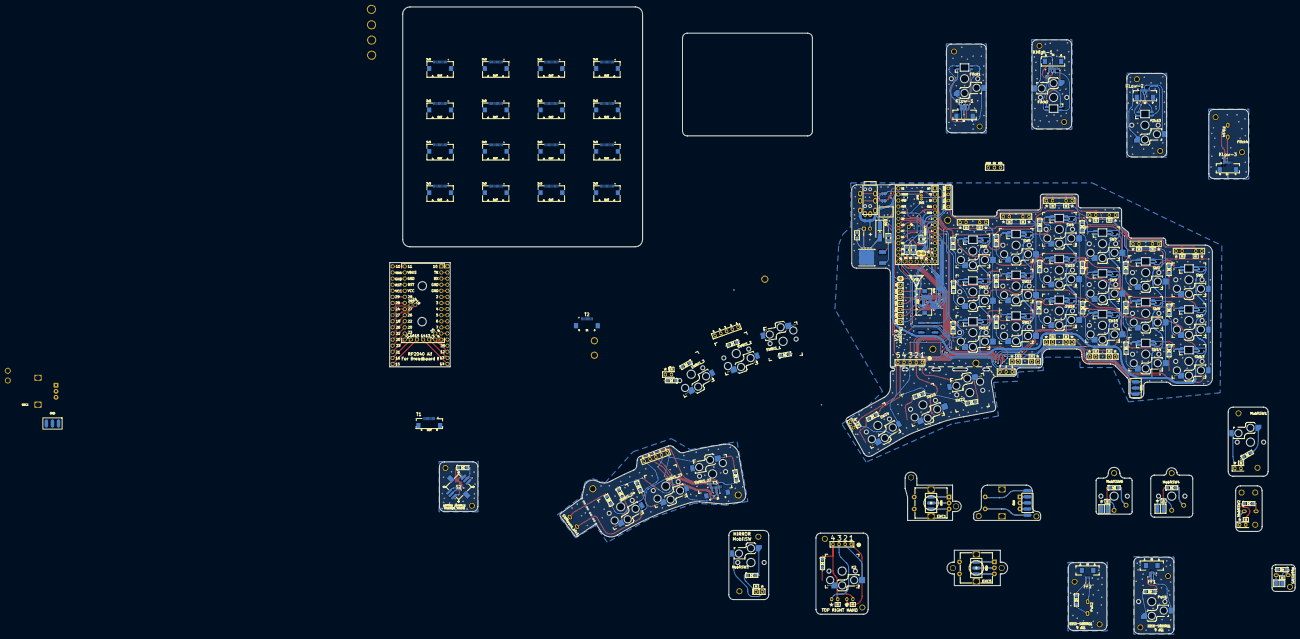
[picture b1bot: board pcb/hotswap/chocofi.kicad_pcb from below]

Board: 2 copper layers, 377.2 x 261.1 mm, 220 parts (5 on the bottom side), 165 nets.
